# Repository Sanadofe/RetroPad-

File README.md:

# RetroPad-
This is RetroPads public repository

**RetroPad**

**Schematics**

**PCB**

**Assembly** 

**Inspirations**
I really wanted to bring vintage and retro tech into the present. This Macropad (RetroPad) allows me to do this, while still looking clean and minimalistic to todays standards. 

**Challenges**
This was my first time trying to make schematics and pcb's. Same goes for the firmware. I think I got there in the end :)

**BOM**
- EC11 Rotary Encoder
- Seeed XIAO RP2040
- 10x MX-Style switches
- 10x through-hole 1N4148 Diodes
- 10x white blank DSA keycaps
- 5x M3x16mm screws
- 5x M3x5mx4mm heatset inserts

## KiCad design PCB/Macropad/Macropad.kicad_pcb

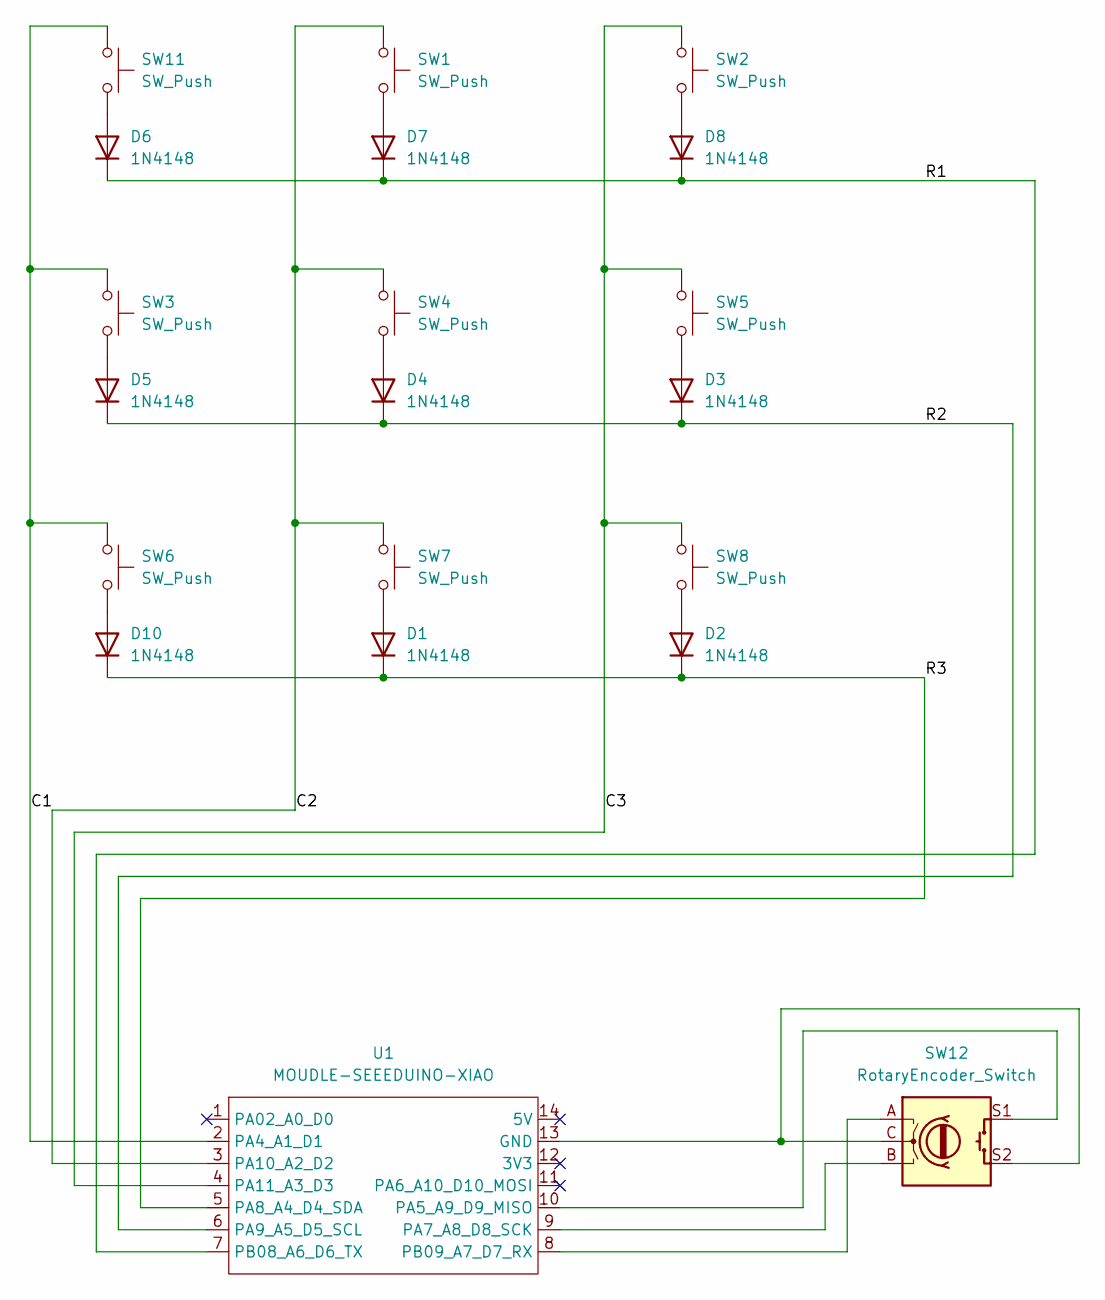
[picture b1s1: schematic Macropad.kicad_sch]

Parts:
D1, D2, D3, D4, D5, D6, D7, D8, D10: 1N4148; D_DO-35_SOD27_P7.62mm_Horizontal
SW1, SW2, SW3, SW4, SW5, SW6, SW7, SW8, SW11: SW_Push; SW_Cherry_MX_1.00u_PCB
SW12: RotaryEncoder_Switch; RotaryEncoder_Alps_EC11E-Switch_Vertical_H20mm
U1: MOUDLE-SEEEDUINO-XIAO; XIAO-Generic-Hybrid-14P-2.54-21X17.8MM

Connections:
/C1: SW3.1, SW6.1, SW11.1, U1.2 (PA4_A1_D1)
/C2: SW1.1, SW4.1, SW7.1, U1.3 (PA10_A2_D2)
/C3: SW2.1, SW5.1, SW8.1, U1.4 (PA11_A3_D3)
/R1: D6.1 (K), D7.1 (K), D8.1 (K), U1.7 (PB08_A6_D6_TX)
/R2: D3.1 (K), D4.1 (K), D5.1 (K), U1.6 (PA9_A5_D5_SCL)
/R3: D1.1 (K), D2.1 (K), D10.1 (K), U1.5 (PA8_A4_D4_SDA)
unnamed: D1.2 (A), SW7.2
unnamed: D2.2 (A), SW8.2
unnamed: D3.2 (A), SW5.2
unnamed: D4.2 (A), SW4.2
unnamed: D5.2 (A), SW3.2
unnamed: D6.2 (A), SW11.2
unnamed: D7.2 (A), SW1.2
unnamed: D8.2 (A), SW2.2
unnamed: D10.2 (A), SW6.2
unnamed: SW12.C, SW12.S2, U1.13 (GND)
unnamed: SW12.S1, U1.10 (PA5_A9_D9_MISO)
unnamed: SW12.B, U1.9 (PA7_A8_D8_SCK)
unnamed: SW12.A, U1.8 (PB09_A7_D7_RX)

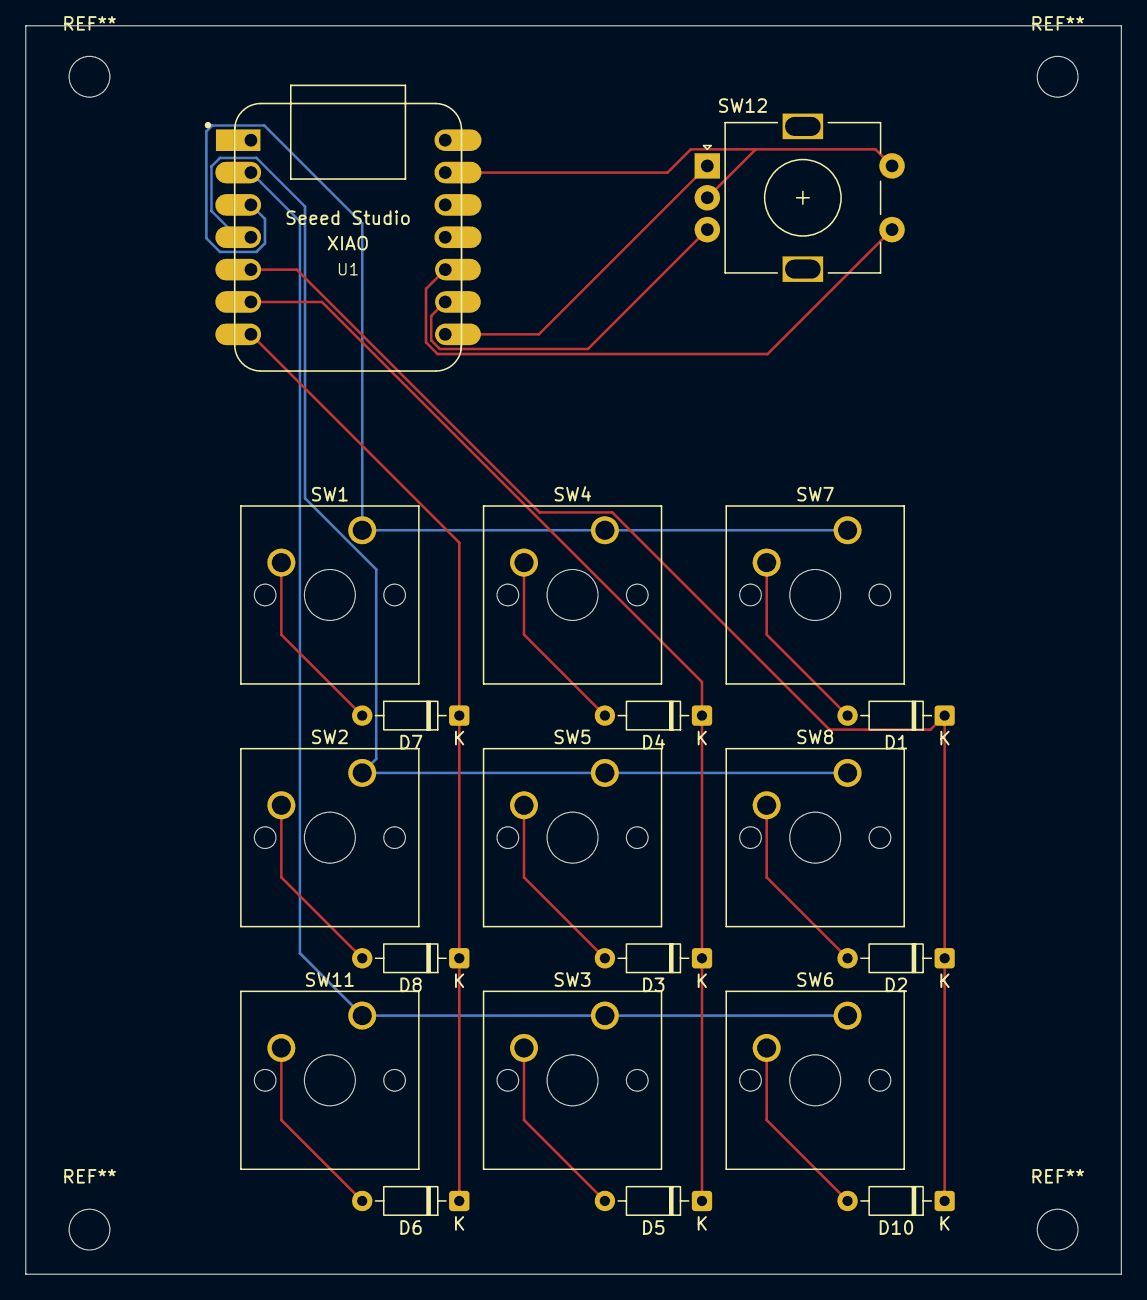
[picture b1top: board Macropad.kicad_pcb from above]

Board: 2 copper layers, 86.0 x 98.0 mm, 20 parts (0 on the bottom side), 19 nets.
